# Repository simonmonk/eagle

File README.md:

eagle
=====

Open Source Design Files and Library to support the book: "Make your Own PCBs with EAGLE" by Simon Monk.

You can find out more information about the book, which describes these designs at

http://www.monkmakes.com/?page_id=567

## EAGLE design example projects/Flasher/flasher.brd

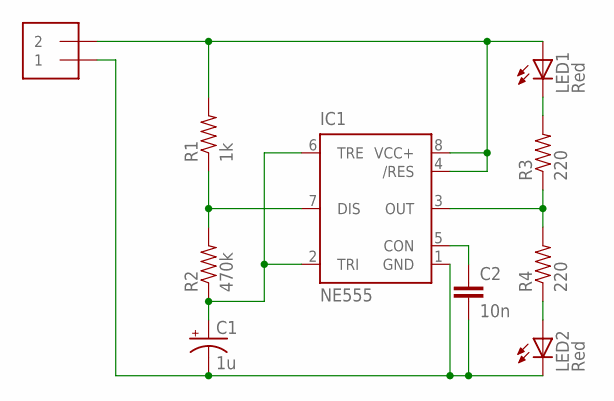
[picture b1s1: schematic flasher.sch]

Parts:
C1: 1u; CPOL-RADIAL-10UF-25V
C2: 10n; CAP-PTH-SMALL
IC1: NE555; DIL-08
J1: 1X2-3.5MM
LED1, LED2: Red; LED5MM
R1: 1k; AXIAL-0.3
R2: 470k; AXIAL-0.3
R3, R4: 220; AXIAL-0.3

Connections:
GND: C1.2 (-), C2.2, IC1.1 (GND), J1.1, LED2.K (C)
unnamed: IC1.3 (OUT), R3.P$1 (1), R4.P$2 (2)
unnamed: LED2.A, R4.P$1 (1)
unnamed: LED1.K (C), R3.P$2 (2)
unnamed: IC1.7 (DIS), R1.P$1 (1), R2.P$2 (2)
unnamed: C1.1 (+), IC1.2 (TRI), IC1.6 (TRE), R2.P$1 (1)
unnamed: C2.1, IC1.5 (CON)
VCC+: IC1.4 (/RES), IC1.8 (VCC+), J1.2, LED1.A, R1.P$2 (2)

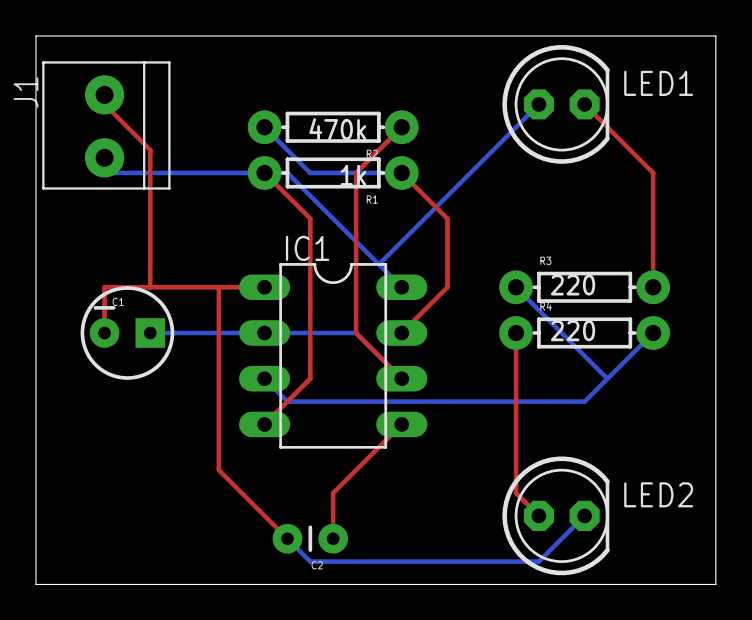
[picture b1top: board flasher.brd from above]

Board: 2 copper layers, 37.8 x 30.5 mm, 10 parts (0 on the bottom side), 8 nets.

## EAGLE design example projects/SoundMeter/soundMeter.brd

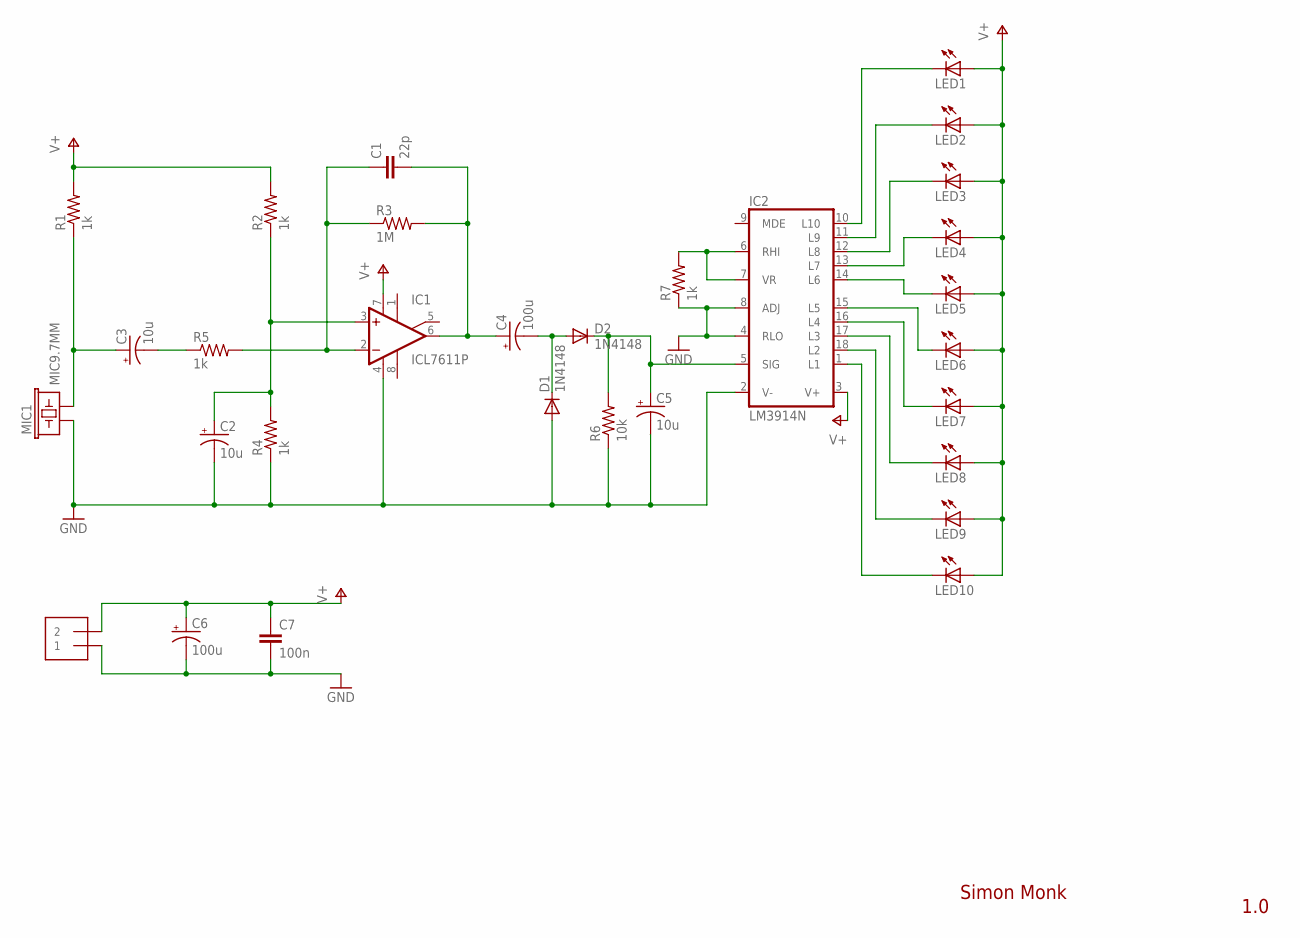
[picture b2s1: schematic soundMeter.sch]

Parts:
C1: 22p; CAP-PTH-SMALL
C2, C3, C5: 10u; CPOL-RADIAL-10UF-25V
C4, C6: 100u; CPOL-RADIAL-10UF-25V
C7: 100n; CAP-PTH-SMALL
D1, D2: 1N4148; DO35-7
IC1: ICL7611P; DIL08
IC2: LM3914N; DIL18
J1: 1X2-3.5MM
LED1, LED2, LED3, LED4, LED5, LED6, LED7, LED8, LED9, LED10: LED3MM
MIC1: MIC9.7MM; MIC-9.7MM
R1, R2, R4, R5, R7: 1k; AXIAL-0.4
R3: 1M; AXIAL-0.4
R6: 10k; AXIAL-0.4

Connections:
GND: C2.2 (-), C5.2 (-), C6.2 (-), C7.2, D1.A, IC1.4 (V-), IC2.2 (V-), IC2.4 (RLO), IC2.8 (ADJ), J1.1, MIC1.1, R4.P$1 (1), R6.P$1 (1), R7.P$1 (1)
unnamed: C4.2 (-), D1.C, D2.A
unnamed: C3.1 (+), MIC1.2, R1.P$1 (1)
unnamed: C5.1 (+), D2.C, IC2.5 (SIG), R6.P$2 (2)
unnamed: C2.1 (+), IC1.3 (+IN), R2.P$1 (1), R4.P$2 (2)
unnamed: C3.2 (-), R5.P$1 (1)
unnamed: C1.1, IC1.2 (-IN), R3.P$1 (1), R5.P$2 (2)
unnamed: C1.2, C4.1 (+), IC1.6 (OUT), R3.P$2 (2)
unnamed: IC2.6 (RHI), IC2.7 (VR), R7.P$2 (2)
unnamed: IC2.10 (L10), LED1.K (C)
unnamed: IC2.11 (L9), LED2.K (C)
unnamed: IC2.12 (L8), LED3.K (C)
unnamed: IC2.13 (L7), LED4.K (C)
unnamed: IC2.14 (L6), LED5.K (C)
unnamed: IC2.15 (L5), LED6.K (C)
unnamed: IC2.16 (L4), LED7.K (C)
unnamed: IC2.17 (L3), LED8.K (C)
unnamed: IC2.18 (L2), LED9.K (C)
unnamed: IC2.1 (L1), LED10.K (C)
V+: C6.1 (+), C7.1, IC1.7 (V+), IC2.3 (V+), J1.2, LED1.A, LED2.A, LED3.A, LED4.A, LED5.A, LED6.A, LED7.A, LED8.A, LED9.A, LED10.A, R1.P$2 (2), R2.P$2 (2)

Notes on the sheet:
Simon Monk
1.0

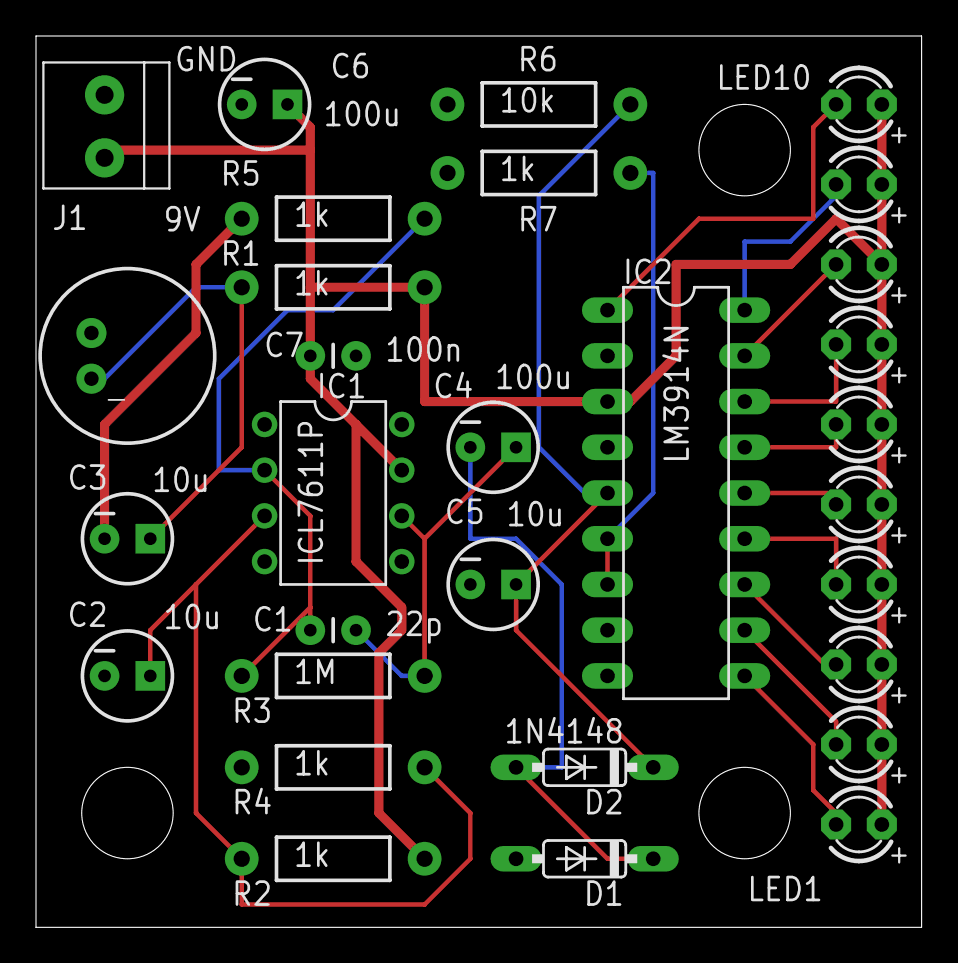
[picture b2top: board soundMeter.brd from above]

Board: 2 copper layers, 49.2 x 49.5 mm, 30 parts (0 on the bottom side), 20 nets.

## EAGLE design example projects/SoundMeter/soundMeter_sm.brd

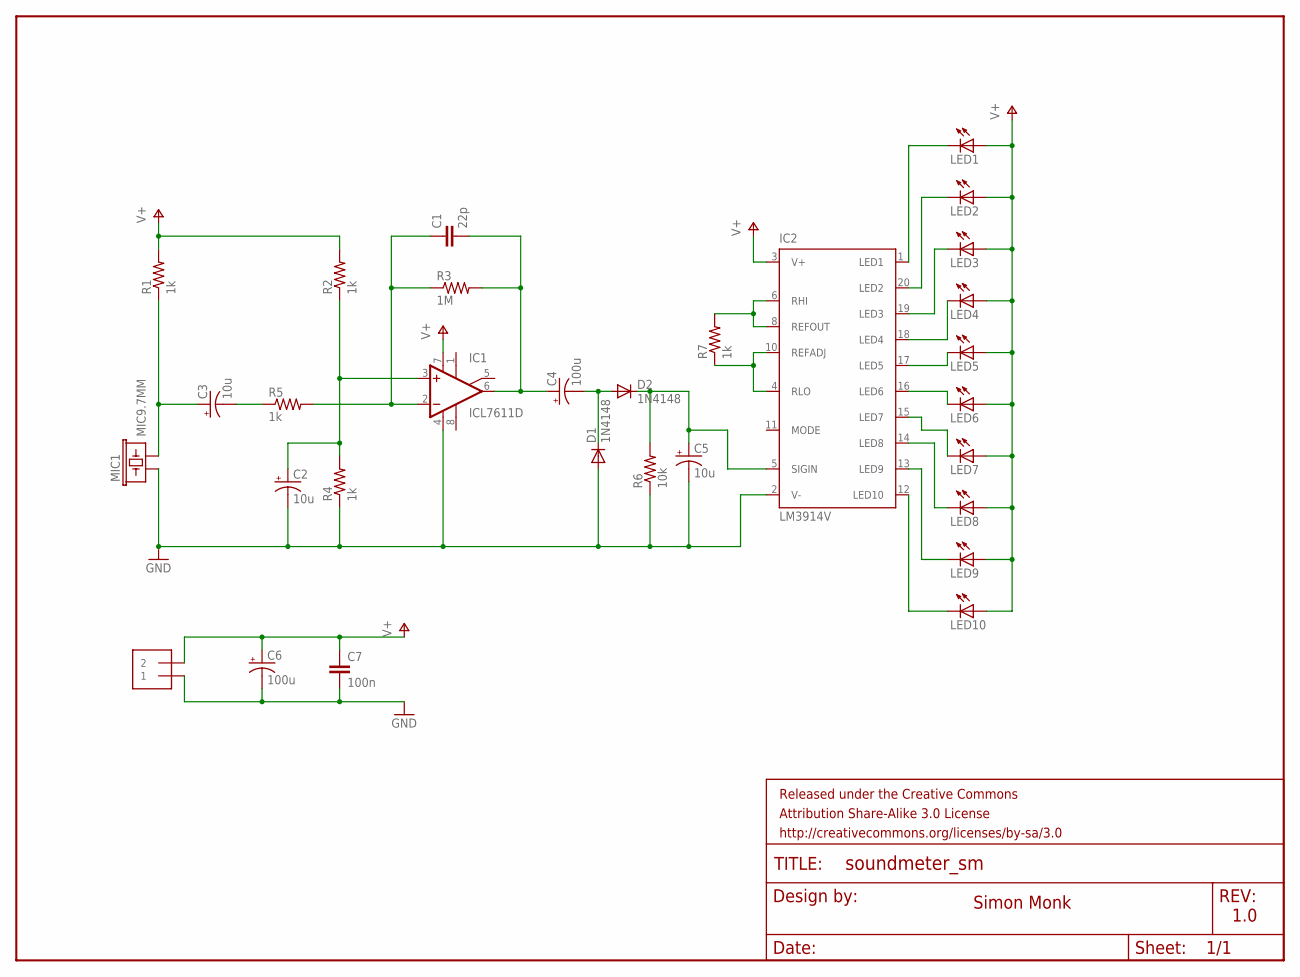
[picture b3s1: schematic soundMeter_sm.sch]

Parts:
C1: 22p; 1206
C2, C3, C5: 10u; PANASONIC_C
C4, C6: 100u; PANASONIC_D
C7: 100n; 1206
D1, D2: 1N4148; SOD-323
FRAME1: FRAME-LETTER; CREATIVE_COMMONS
IC1: ICL7611D; SO08
IC2: LM3914V; PLCC20S
J1: 1X2-3.5MM
LED1, LED2, LED3, LED4, LED5, LED6, LED7, LED8, LED9, LED10: LED1206; LED-1206
MIC1: MIC9.7MM; MIC-9.7MM
R1, R2, R4, R5, R7: 1k; 1206
R3: 1M; 1206
R6: 10k; 1206

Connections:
GND: C2.-, C5.-, C6.-, C7.2, D1.2 (A), IC1.4 (V-), IC2.2 (V-), J1.1, MIC1.1, R4.1, R6.1
unnamed: C4.-, D1.1 (C), D2.2 (A)
unnamed: C3.+, MIC1.2, R1.1
unnamed: C5.+, D2.1 (C), IC2.5 (SIGIN), R6.2
unnamed: C2.+, IC1.3 (+IN), R2.1, R4.2
unnamed: C3.-, R5.1
unnamed: C1.1, IC1.2 (-IN), R3.1, R5.2
unnamed: C1.2, C4.+, IC1.6 (OUT), R3.2
unnamed: IC2.12 (LED10), LED10.C
unnamed: IC2.13 (LED9), LED9.C
unnamed: IC2.14 (LED8), LED8.C
unnamed: IC2.15 (LED7), LED7.C
unnamed: IC2.16 (LED6), LED6.C
unnamed: IC2.17 (LED5), LED5.C
unnamed: IC2.18 (LED4), LED4.C
unnamed: IC2.19 (LED3), LED3.C
unnamed: IC2.20 (LED2), LED2.C
unnamed: IC2.1 (LED1), LED1.C
unnamed: IC2.4 (RLO), IC2.10 (REFADJ), R7.1
unnamed: IC2.6 (RHI), IC2.8 (REFOUT), R7.2
V+: C6.+, C7.1, IC1.7 (V+), IC2.3 (V+), J1.2, LED1.A, LED2.A, LED3.A, LED4.A, LED5.A, LED6.A, LED7.A, LED8.A, LED9.A, LED10.A, R1.2, R2.2

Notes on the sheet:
Simon Monk
1.0

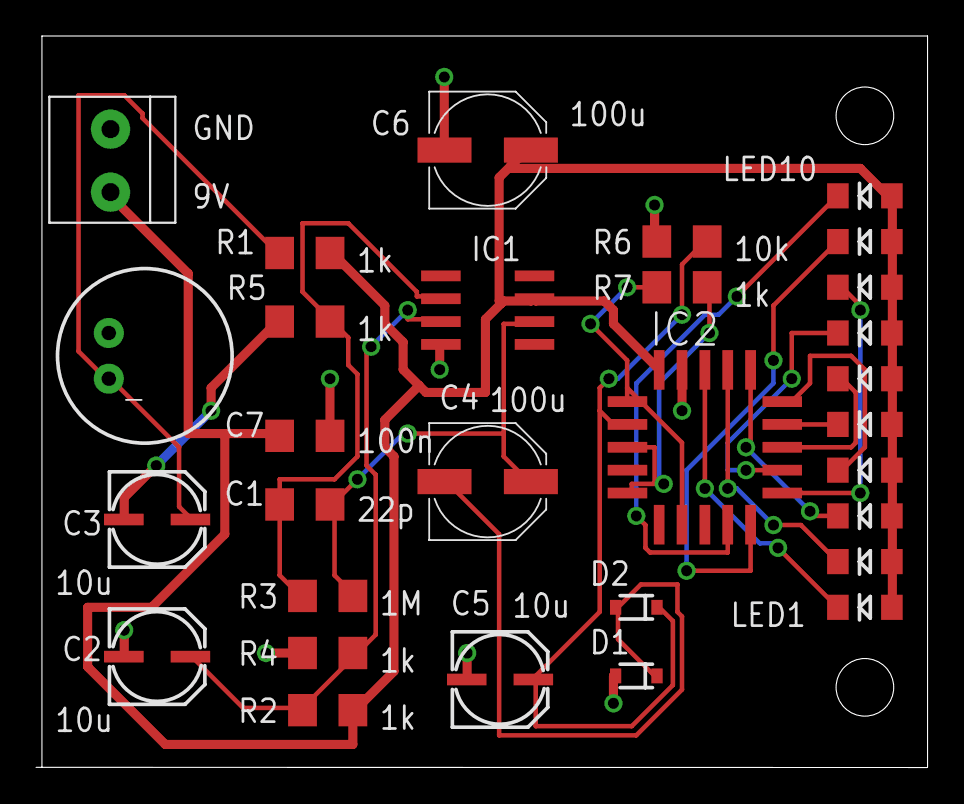
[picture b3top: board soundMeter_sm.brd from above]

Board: 2 copper layers, 49.5 x 40.6 mm, 31 parts (0 on the bottom side), 21 nets.

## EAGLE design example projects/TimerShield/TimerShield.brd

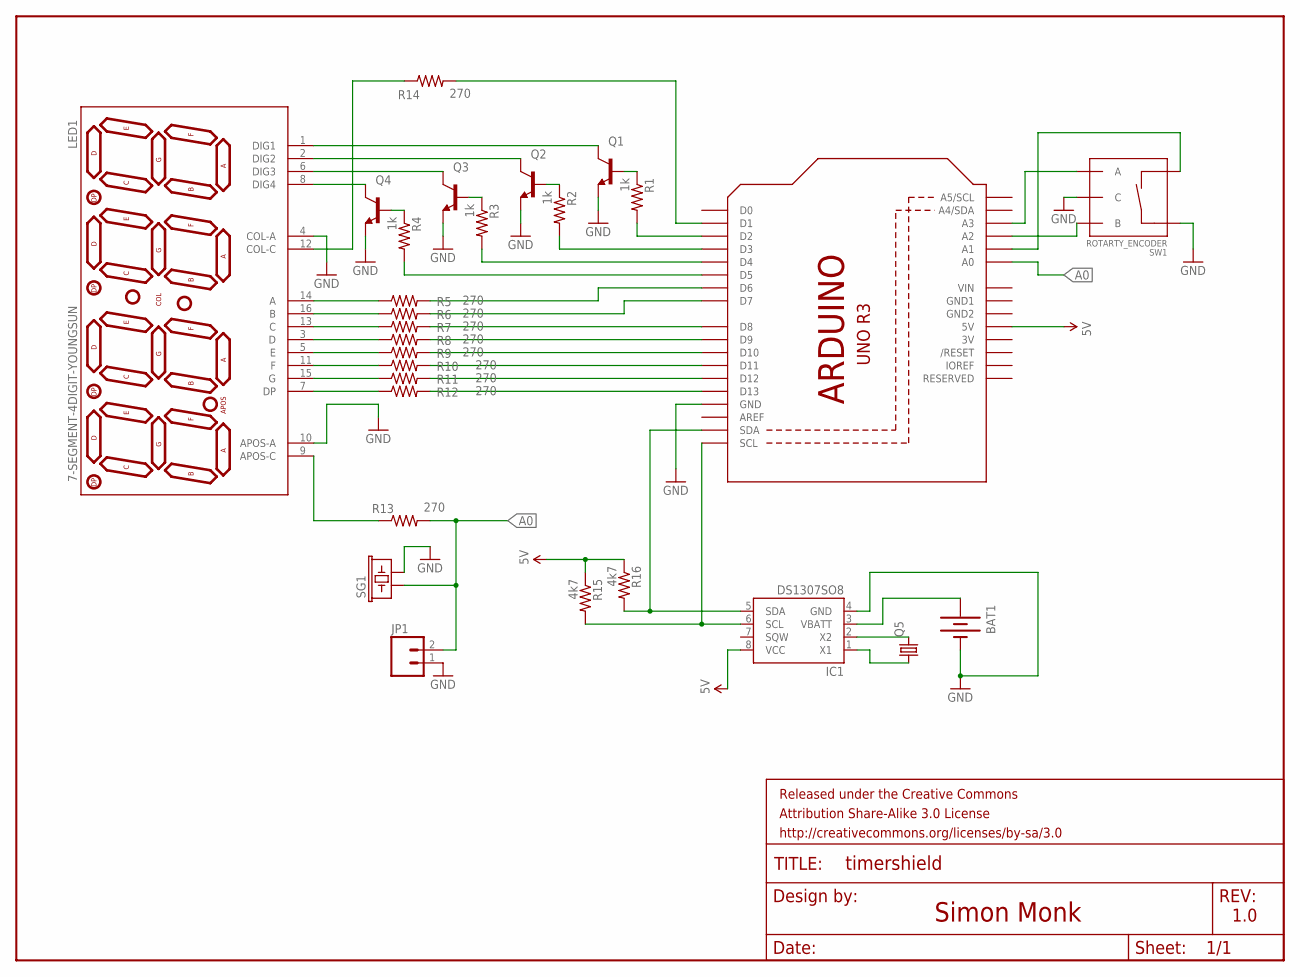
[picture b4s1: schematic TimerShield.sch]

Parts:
BAT1: BATTERY12MM; BATTCON_12MM
FRAME1: FRAME-LETTER; CREATIVE_COMMONS
IC1: DS1307SO8; SO08
JP1: M023.5MM; SCREWTERMINAL-3.5MM-2
LED1: 7-SEGMENT-4DIGIT-YOUNGSUN
Q1, Q2, Q3, Q4: TRANSISTOR_NPNSOT23; SOT23
Q5: CRYSTALTC26H; TC26H
R1, R2, R3, R4: 1k; 0805
R5, R6, R7, R8, R9, R10, R11, R12, R13, R14: 270; 0805
R15, R16: 4k7; 0805
SG1: BUZZERNS; BUZZER-12MM-NS
SW1: ROTARTY_ENCODER; ROTARY_ENC_PLAIN
U1: ARDUINOR3-DIMENSION; ARDUINOR3

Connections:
3V: U1.3V
5V: IC1.8 (VCC), R15.1, R16.1, U1.5V
A0: JP1.2, R13.2, SG1.+ (1), U1.A0
GND: BAT1.GND (-), IC1.4 (GND), JP1.1, LED1.4 (COL-A), LED1.10 (APOS-A), Q1.2 (E), Q2.2 (E), Q3.2 (E), Q4.2 (E), SG1.- (2), SW1.C, SW1.SW+, U1.GND
GND1: U1.GND1
GND2: U1.GND2
unnamed: LED1.8 (DIG4), Q4.3 (C)
unnamed: LED1.6 (DIG3), Q3.3 (C)
unnamed: LED1.2 (DIG2), Q2.3 (C)
unnamed: LED1.1 (DIG1), Q1.3 (C)
unnamed: Q4.1 (B), R4.1
unnamed: Q3.1 (B), R3.1
unnamed: Q2.1 (B), R2.1
unnamed: Q1.1 (B), R1.1
unnamed: R1.2, U1.D2
unnamed: R2.2, U1.D3
unnamed: R3.2, U1.D4
unnamed: R4.2, U1.D5
unnamed: LED1.14 (A), R5.1
unnamed: LED1.16 (B), R6.1
unnamed: LED1.13 (C), R7.1
unnamed: LED1.3 (D), R8.1
unnamed: LED1.5 (E), R9.1
unnamed: LED1.11 (F), R10.1
unnamed: LED1.15 (G), R11.1
unnamed: LED1.7 (DP), R12.1
unnamed: R5.2, U1.D6
unnamed: R6.2, U1.D7
unnamed: R7.2, U1.D8
unnamed: R8.2, U1.D9
unnamed: R9.2, U1.D10
unnamed: R10.2, U1.D11
unnamed: R11.2, U1.D12
unnamed: R12.2, U1.D13
unnamed: LED1.12 (COL-C), R14.1
unnamed: SW1.A, U1.A3
unnamed: SW1.B, U1.A2
unnamed: R14.2, U1.D1
unnamed: SW1.SW-, U1.A1
unnamed: IC1.2 (X2), Q5.2
unnamed: IC1.1 (X1), Q5.1
unnamed: IC1.6 (SCL), R15.2, U1.SCL
unnamed: IC1.5 (SDA), R16.2, U1.SDA
unnamed: LED1.9 (APOS-C), R13.1
unnamed: BAT1.PWR@1 (+), IC1.3 (VBATT)
VIN: U1.VIN

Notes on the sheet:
Simon Monk
1.0

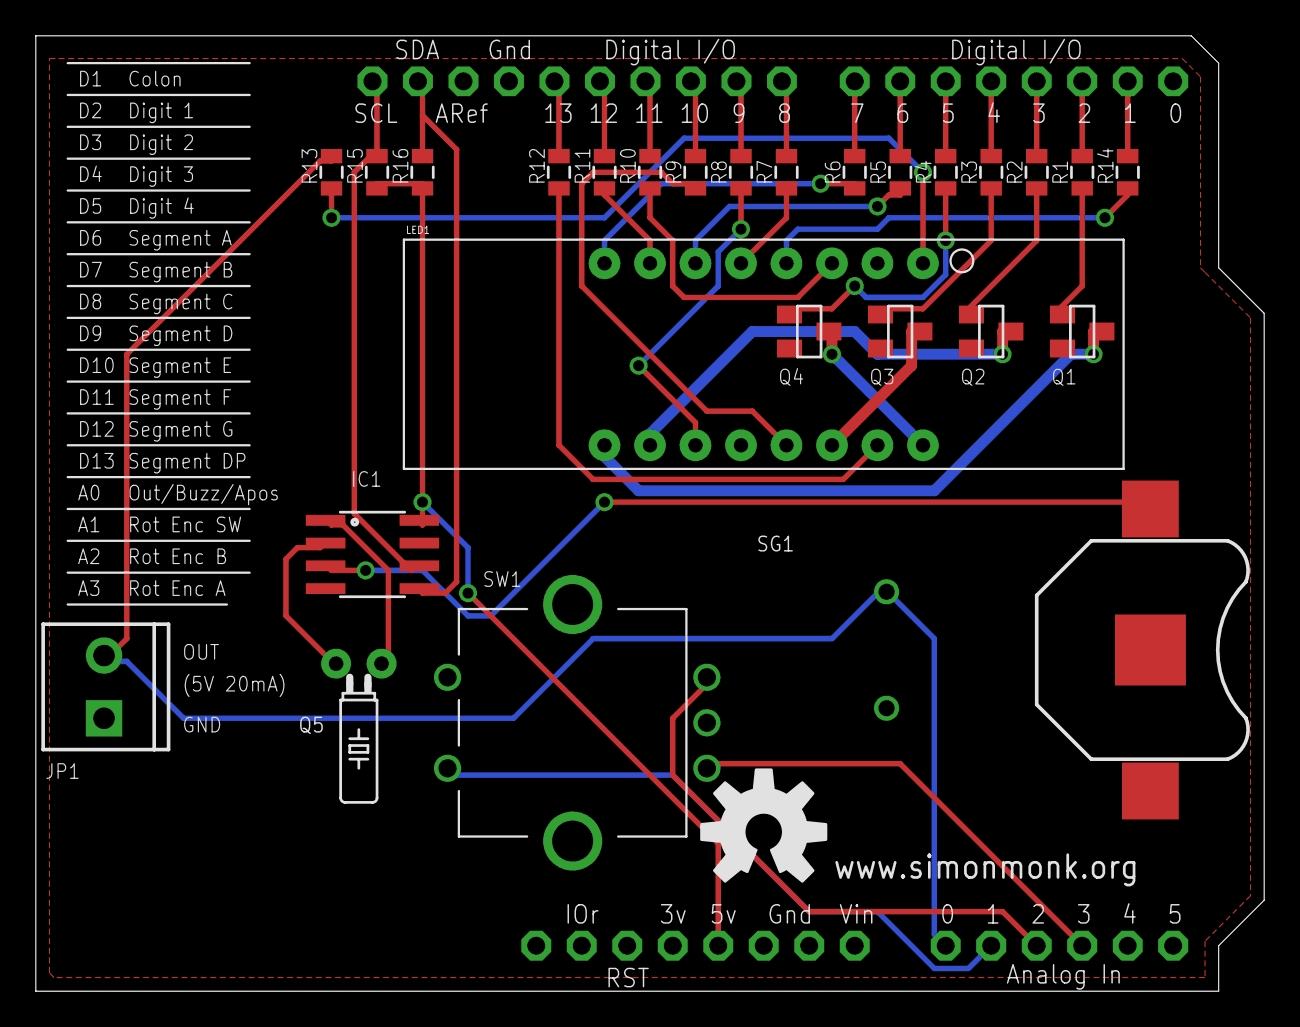
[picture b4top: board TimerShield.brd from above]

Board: 2 copper layers, 68.6 x 53.3 mm, 30 parts (0 on the bottom side), 42 nets.

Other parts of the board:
U$1: OSHW-LOGO-L

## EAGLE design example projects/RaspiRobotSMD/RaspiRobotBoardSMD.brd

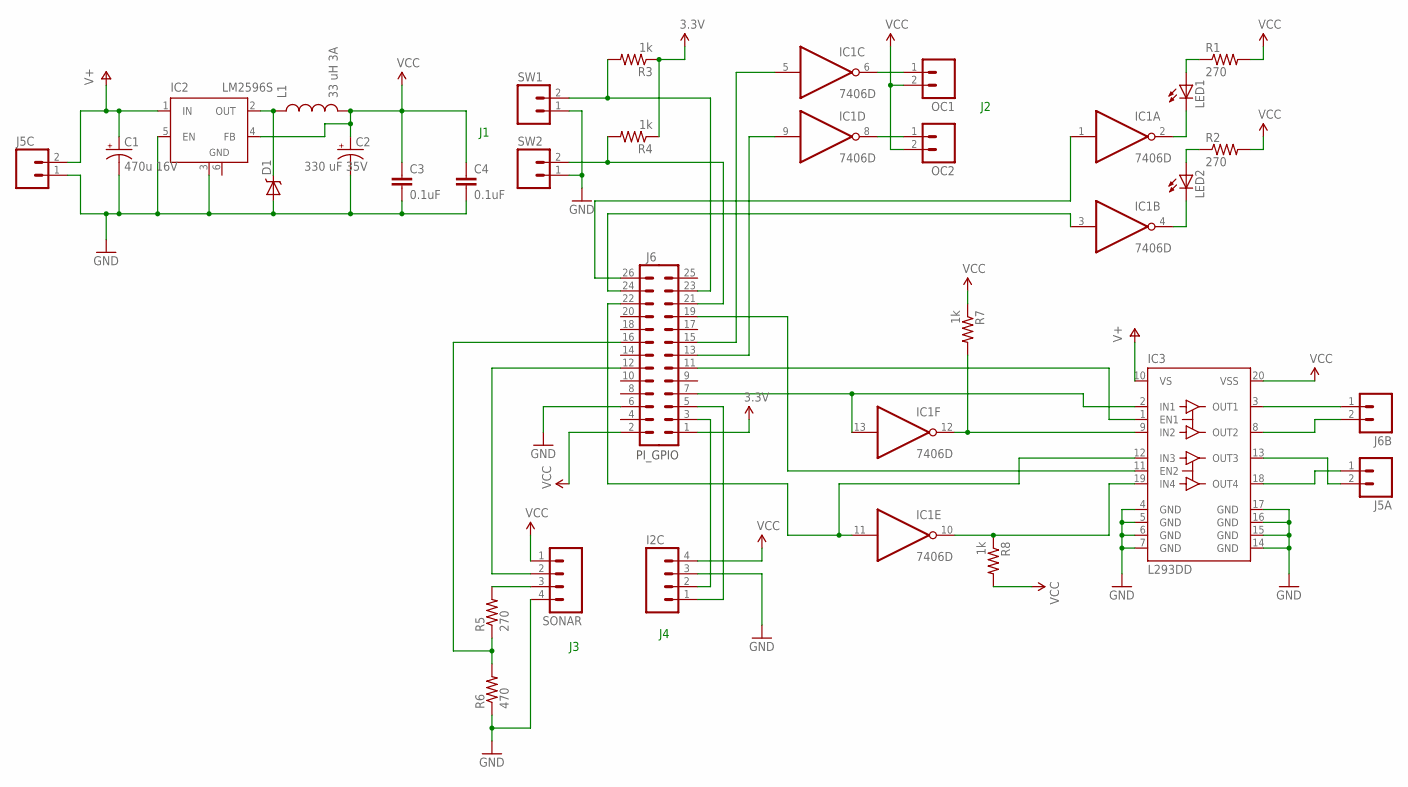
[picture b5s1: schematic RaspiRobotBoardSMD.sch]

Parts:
C1: 470u 16V; PANASONIC_E
C2: 330 uF 35V; PANASONIC_G
C3, C4: 0.1uF; 0805
D1: B340A; SMA-DIODE
I2C: M04PTH; 1X04
IC1: 7406D; SO14
IC2: LM2596S; TO263-5
IC3: L293DD; SO20
J5A, J5C, J6B: M023.5MM_LOCK; SCREWTERMINAL-3.5MM-2_LOCK
J6: M13X22X13; 2X13
L1: 33 uH 3A; CDRH125
LED1, LED2: LEDSMT1206; 1206
OC1, OC2: M02PTH; 1X02
R1, R2, R5: 270; 0805
R3, R4, R7, R8: 1k; 0805
R6: 470; 0805
SONAR: M04PTH; 1X04
SW1, SW2: M02PTH; 1X02

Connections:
3.3V: J6.1, R3.1, R4.1
GND: C1.-, C2.-, C3.2, C4.2, D1.A, I2C.3, IC1.7 (GND), IC2.3 (GND), IC2.5 (EN), IC2.6 (GND), IC3.4 (GND), IC3.5 (GND), IC3.6 (GND), IC3.7 (GND), IC3.14 (GND), IC3.15 (GND), IC3.16 (GND), IC3.17 (GND), J5C.1, J6.6, R6.1, SONAR.4, SW1.1, SW2.1
unnamed: D1.C, IC2.2 (OUT), L1.1
unnamed: IC3.3 (OUT1), J6B.1
unnamed: IC3.8 (OUT2), J6B.2
unnamed: IC3.18 (OUT4), J5A.1
unnamed: IC1.13 (I), IC3.2 (IN1), J6.7
unnamed: IC1.12 (O), IC3.9 (IN2), R7.2
unnamed: IC1.10 (O), IC3.19 (IN4), R8.1
unnamed: IC1.11 (I), IC3.12 (IN3), J6.22
unnamed: LED1.A, R1.1
unnamed: LED2.A, R2.1
unnamed: IC1.2 (O), LED1.C
unnamed: IC1.4 (O), LED2.C
unnamed: IC1.6 (O), OC1.1
unnamed: IC1.8 (O), OC2.1
unnamed: J6.23, R3.2, SW1.2
unnamed: J6.21, R4.2, SW2.2
unnamed: IC1.3 (I), J6.24
unnamed: J6.16, R5.1, R6.2
unnamed: J6.12, SONAR.2
unnamed: R5.2, SONAR.3
unnamed: IC1.1 (I), J6.26
unnamed: IC3.1 (EN1), J6.11
unnamed: IC3.11 (EN2), J6.19
unnamed: IC1.9 (I), J6.13
unnamed: IC1.5 (I), J6.15
unnamed: I2C.2, J6.3
unnamed: I2C.1, J6.5
unnamed: IC3.13 (OUT3), J5A.2
V+: C1.+, IC2.1 (IN), IC3.10 (VS), J5C.2
VCC: C2.+, C3.1, C4.1, I2C.4, IC1.14 (VCC), IC2.4 (FB), IC3.20 (VSS), J6.2, L1.2, OC1.2, OC2.2, R1.2, R2.2, R7.1, R8.2, SONAR.1

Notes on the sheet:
PI_GPIO

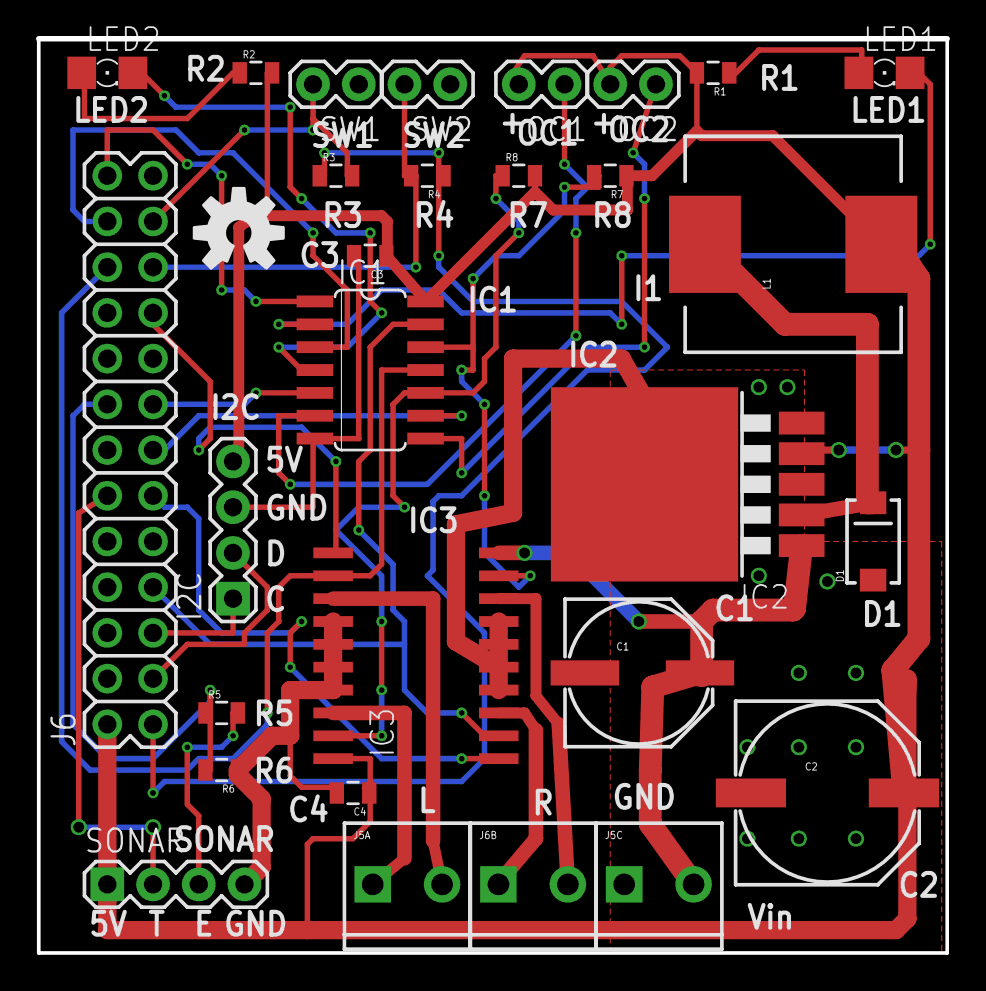
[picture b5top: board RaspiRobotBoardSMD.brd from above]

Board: 2 copper layers, 50.5 x 50.8 mm, 30 parts (0 on the bottom side), 32 nets.

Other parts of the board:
U$1: OSHW-LOGO-M

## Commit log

2014-04-30 first upload

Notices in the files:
parts and their libraries:
SparkFun-Passives: Licensing: CC v3.0 Share-Alike You are welcome to use this library for commercial purposes.
SparkFun-Aesthetics: Released under the Creative Commons Attribution Share-Alike 3.0 License
SparkFun-Aesthetics: http://creativecommons.org/licenses/by-sa/3.0
